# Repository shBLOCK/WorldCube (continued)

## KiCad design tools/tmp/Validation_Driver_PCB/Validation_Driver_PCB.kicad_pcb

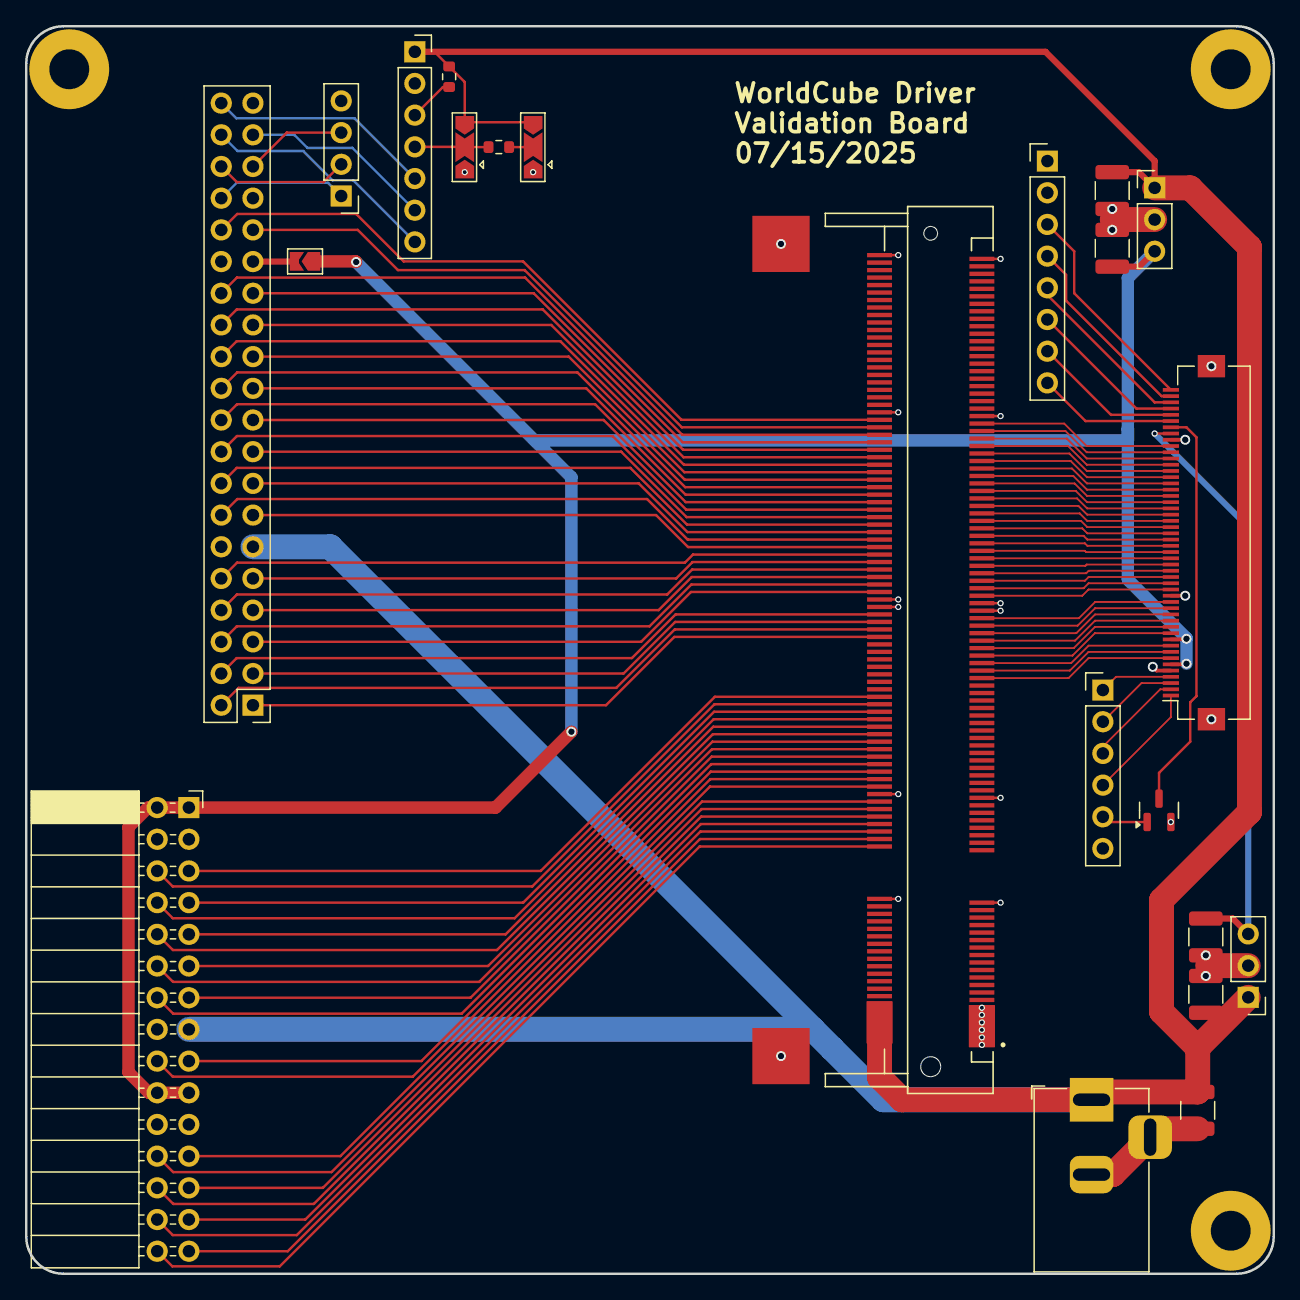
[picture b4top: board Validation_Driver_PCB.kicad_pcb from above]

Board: 4 copper layers, 100.0 x 100.0 mm, 25 parts (0 on the bottom side), 107 nets.

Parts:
C1, C2, C3, C4, C5: 47uF 25V; C_1210_3225Metric
H1, H2, H3: MountingHole_Pad; MountingHole_3.2mm_M3_Pad
J1: ICESugar-Pro; TE_1565917-4
J2: VC-ADV7611; PinHeader_2x20_P2.54mm_Vertical
J4: MAX98357_Module; PinSocket_1x07_P2.54mm_Vertical
J7: FPC_50Pin; Hirose_FH12-50S-0.5SH_1x50-1MP_P0.50mm_Horizontal
J8: Misc; PinHeader_1x08_P2.54mm_Vertical
J9: LCD_Ctrl; PinHeader_1x06_P2.54mm_Vertical
J10: ADV7611_Init; PinHeader_1x04_P2.54mm_Vertical
J11: LCD_BL_DCDC; PinHeader_1x03_P2.54mm_Vertical
J12: 3V3_DCDC; PinHeader_1x03_P2.54mm_Vertical
J14: FPGA_GPIO; PinSocket_2x15_P2.54mm_Horizontal
J15: 5V_IN; BarrelJack_Horizontal
JP3: SolderJumper_2_Open; SolderJumper-2_P1.3mm_Open_TrianglePad1.0x1.5mm
JP4, JP5: SolderJumper_3_Open; SolderJumper-3_P2.0mm_Open_TrianglePad1.0x1.5mm
Q1: AO3400A; SOT-23
R1: 100k; R_0603_1608Metric
R2: 1M; R_0603_1608Metric

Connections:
+3V3: C4.1, J7.6, J7.10, J12.3, J14.1, J14.2, J14.19, J14.20, JP3.1 (A)
+5V: C1.1, C3.1, C5.1, J1.2, J1.4, J1.6, J1.8, J1.10, J1.12, J2.11, J4.1, J11.1, J12.1, J14.15, J15.1, JP4.3 (B), JP5.3 (B), R2.1
ADV7611_SCL: J2.36, J10.2
ADV7611_SDA: J2.35, J10.3
ADV7611_~RST: J2.34, J10.1
FPGA_GPIO_0: J1.82, J14.5
FPGA_GPIO_1: J1.80, J14.6
FPGA_GPIO_2: J1.78, J14.7
FPGA_GPIO_3: J1.76, J14.8
FPGA_GPIO_4: J1.74, J14.9
FPGA_GPIO_5: J1.72, J14.10
FPGA_GPIO_6: J1.70, J14.11
FPGA_GPIO_7: J1.68, J14.12
FPGA_GPIO_8: J1.66, J14.13
FPGA_GPIO_9: J1.64, J14.14
FPGA_GPIO_10: J1.62, J14.17
FPGA_GPIO_11: J1.60, J14.18
FPGA_GPIO_12: J1.58, J14.23
FPGA_GPIO_13: J1.54, J14.24
FPGA_GPIO_14: J1.52, J14.25
FPGA_GPIO_15: J1.50, J14.26
FPGA_GPIO_16: J1.48, J14.27
FPGA_GPIO_17: J1.46, J14.28
FPGA_GPIO_18: J1.44, J14.29
FPGA_GPIO_19: J1.42, J14.30
GND: C1.2, C2.2, C3.2, C4.2, C5.2, H1.1, H2.1, H3.1, J1.1, J1.3, J1.5, J1.7, J1.9, J1.11, J1.39, J1.40, J1.55, J1.56, J1.105, J1.106, J1.107, J1.108, J1.157, J1.158, J1.199, J1.200, J1.SH1 (SHIELD), J1.SH2 (SHIELD), J2.12, J2.30, J4.2, J7.5, J7.17, J7.42, J7.MP (MountPin), J8.1, J8.2, J9.6, J10.4, J11.2, J12.2, J14.3, J14.4, J14.16, J14.21, J14.22, J15.2, J15.3, JP4.1 (A), JP5.1 (A), Q1.2 (S)
I2S_DIN: J2.40, J4.5
I2S_LRCLK: J2.38, J4.7
I2S_SCLK: J2.37, J4.6
LCD_BL_CTL: J9.5, Q1.1 (G)
LCD_BL_P: C2.1, J7.43, J11.3
LCD_D0: J1.155, J7.41
LCD_D1: J1.153, J7.40
LCD_D2: J1.151, J7.39
LCD_D3: J1.149, J7.38
LCD_D4: J1.147, J7.37
LCD_D5: J1.145, J7.36
LCD_D6: J1.143, J7.35
LCD_D7: J1.141, J7.34
LCD_D8: J1.139, J7.33
LCD_D9: J1.137, J7.32
LCD_D10: J1.135, J7.31
LCD_D11: J1.133, J7.30
LCD_D12: J1.131, J7.29
LCD_D13: J1.129, J7.28
LCD_D14: J1.127, J7.27
LCD_D15: J1.125, J7.26
LCD_D16: J1.123, J7.25
LCD_D17: J1.121, J7.24
LCD_D18: J1.119, J7.23
LCD_D19: J1.117, J7.22
LCD_D20: J1.115, J7.21
LCD_D21: J1.113, J7.20
LCD_D22: J1.111, J7.19
LCD_D23: J1.109, J7.18
LCD_DE: J1.87, J7.7
LCD_HSYNC: J1.91, J7.9
LCD_PCLK_0: J1.103, J7.16
LCD_PCLK_1: J1.101, J7.15
LCD_PCLK_2: J1.99, J7.14
LCD_PCLK_3: J1.97, J7.13
LCD_PCLK_4: J1.95, J7.12
LCD_PCLK_5: J1.93, J7.11
LCD_SCL: J7.2, J9.3
LCD_SDA: J7.1, J9.4
LCD_VSYNC: J1.89, J7.8
LCD_~CS: J7.3, J9.2
LCD_~RST: J7.4, J9.1
unnamed: J2.29, JP3.2 (B)
unnamed: J4.3, R2.2
unnamed: J4.4, JP4.2 (C), R1.2
unnamed: J7.44, Q1.3 (D)
unnamed: J7.45, J8.8
unnamed: J7.46, J8.7
unnamed: J7.47, J8.6
unnamed: J7.48, J8.5
unnamed: J7.49, J8.4
unnamed: J7.50, J8.3
unnamed: JP5.2 (C), R1.1
VIDIN_D0: J1.148, J2.26
VIDIN_D1: J1.146, J2.25
VIDIN_D2: J1.144, J2.24
VIDIN_D3: J1.142, J2.23
VIDIN_D4: J1.140, J2.22
VIDIN_D5: J1.138, J2.21
VIDIN_D6: J1.136, J2.20
VIDIN_D7: J1.134, J2.19
VIDIN_D8: J1.132, J2.18
VIDIN_D9: J1.130, J2.17
VIDIN_D10: J1.128, J2.16
VIDIN_D11: J1.126, J2.15
VIDIN_D12: J1.124, J2.14
VIDIN_D13: J1.122, J2.13
VIDIN_D14: J1.120, J2.10
VIDIN_D15: J1.118, J2.9
VIDIN_D16: J1.116, J2.8
VIDIN_D17: J1.114, J2.7
VIDIN_D18: J1.112, J2.6
VIDIN_D19: J1.110, J2.5
VIDIN_D20: J1.104, J2.4
VIDIN_D21: J1.102, J2.3
VIDIN_D22: J1.100, J2.2
VIDIN_D23: J1.98, J2.1
VIDIN_DE: J1.156, J2.32
VIDIN_HS: J1.154, J2.31
VIDIN_PCLK: J1.150, J2.27
VIDIN_VS: J1.152, J2.28

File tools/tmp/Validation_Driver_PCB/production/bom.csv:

Designator,Footprint,Quantity,Value,LCSC Part #
"C1, C2, C3, C4, C5",1210,5,47uF 25V,C7432791
J1,TE_1565917-4,1,ICESugar-Pro,
J10,PinHeader_1x04_P2.54mm_Vertical,1,ADV7611_Init,
J11,PinHeader_1x03_P2.54mm_Vertical,1,LCD_BL_DCDC,
J12,PinHeader_1x03_P2.54mm_Vertical,1,3V3_DCDC,
J14,PinSocket_2x15_P2.54mm_Horizontal,1,FPGA_GPIO,
J15,BarrelJack_Horizontal,1,5V_IN,
J2,PinHeader_2x20_P2.54mm_Vertical,1,VC-ADV7611,
J4,PinSocket_1x07_P2.54mm_Vertical,1,MAX98357_Module,
J7,Hirose_FH12-50S-0.5SH_1x50-1MP_P0.50mm_Horizontal,1,FPC_50Pin,C231436
J8,PinHeader_1x08_P2.54mm_Vertical,1,Misc,
J9,PinHeader_1x06_P2.54mm_Vertical,1,LCD_Ctrl,
Q1,SOT-23,1,AO3400A,C20917
R1,0603,1,100k,
R2,0603,1,1M,

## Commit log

2025-07-09 Amaranth environment & SwappableDoubleBufferMemory
2025-07-09 Update .idea folder content
2025-07-09 Reference docs
2025-07-09 Add `micropython-tools-settings.xml`
2025-07-10 FPGA parallel bus LCD driver work
2025-07-22 Still debugging video splitter...
2025-07-24 FlipGo demo working in Godot!
2025-07-25 Change CRLF to LF
2025-07-25 Add missing dependencies
2025-07-25 Ignore .idea directory
2025-07-25 Change CRLF to LF (again)
2025-07-25 Experiment with ball projectile idea
2025-07-25 Add flashlight
2025-07-26 Update.......................................................................................................
2026-03-03 New prototype PCB progress
2026-03-05 tauri-media-pipe-face progress
